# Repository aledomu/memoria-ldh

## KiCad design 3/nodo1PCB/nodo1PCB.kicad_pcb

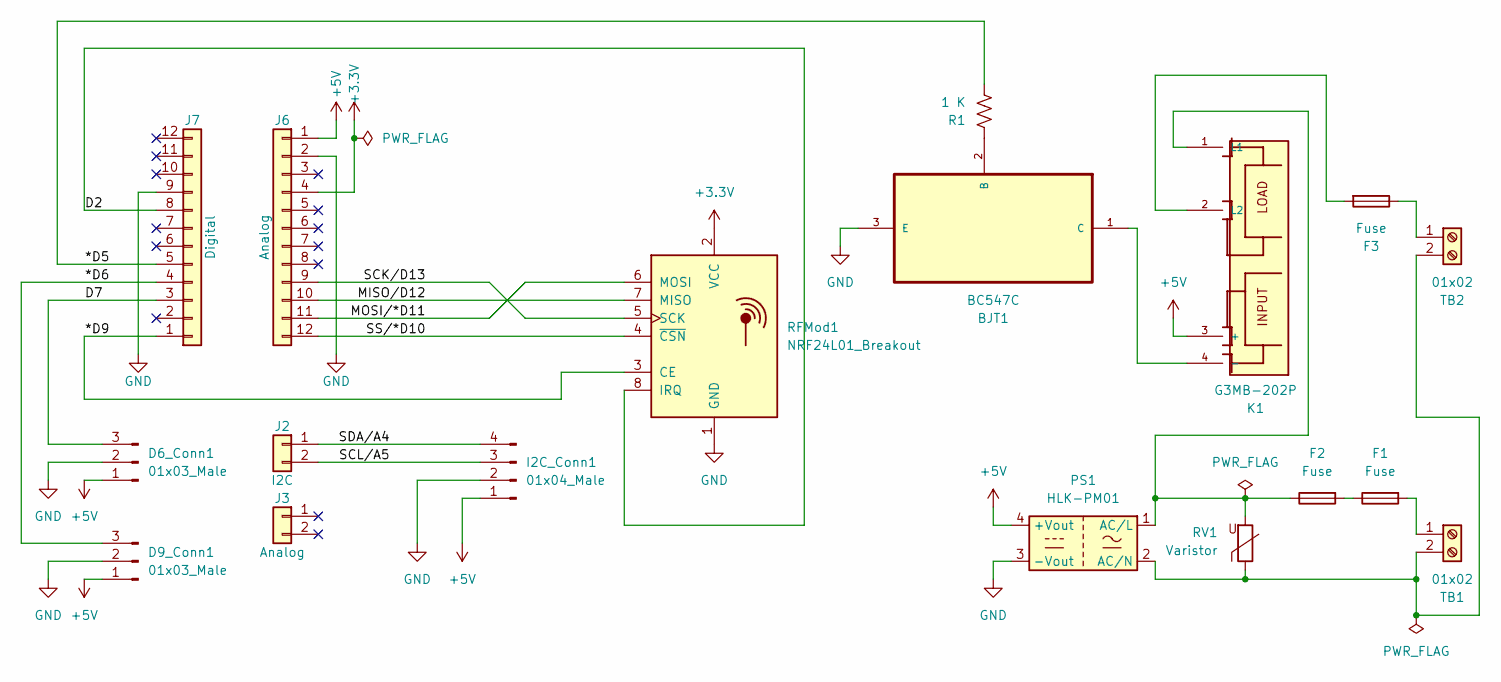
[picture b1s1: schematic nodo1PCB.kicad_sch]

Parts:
BJT1: BC547C; TO127P254X732-3; MPN BC547C
D6_Conn1, D9_Conn1: 01x03_Male; PinHeader_1x03_P2.54mm_Vertical
F1, F2, F3: Fuse; R_Axial_DIN0414_L11.9mm_D4.5mm_P15.24mm_Horizontal
I2C_Conn1: 01x04_Male; PinHeader_1x04_P2.54mm_Vertical
J2: I2C; PinHeader_1x02_P2.54mm_Vertical
J3: Analog; PinHeader_1x02_P2.54mm_Vertical
J6: Analog; PinHeader_1x12_P2.54mm_Vertical
J7: Digital; PinHeader_1x12_P2.54mm_Vertical
K1: G3MB-202P; RELAY_G3MB-202P
PS1: HLK-PM01; Converter_ACDC_HiLink_HLK-PMxx
R1: 1 K; R_1206_3216Metric_Pad1.30x1.75mm_HandSolder
RFMod1: NRF24L01_Breakout; nRF24L01_Breakout
RV1: Varistor; RV_Disc_D12mm_W6.2mm_P7.5mm
TB1, TB2: 01x02; TerminalBlock_bornier-2_P5.08mm

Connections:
+3.3V: J6.4, RFMod1.2 (VCC)
+5V: D6_Conn1.1, D9_Conn1.1, I2C_Conn1.1, J6.1, K1.3 (+), PS1.4 (+Vout)
/*D5: J7.5, R1.2
/*D6: D9_Conn1.3, J7.4
/*D9: J7.1, RFMod1.3 (CE)
/D2: J7.8, RFMod1.8 (IRQ)
/D7: D6_Conn1.3, J7.3
/MISO/D12: J6.10, RFMod1.7 (MISO)
/MOSI/*D11: J6.11, RFMod1.6 (MOSI)
/SCK/D13: J6.9, RFMod1.5 (SCK)
/SCL/A5: I2C_Conn1.3, J2.2
/SDA/A4: I2C_Conn1.4, J2.1
/SS/*D10: J6.12, RFMod1.4 (~CSN)
GND: BJT1.3 (E), D6_Conn1.2, D9_Conn1.2, I2C_Conn1.2, J6.2, J7.9, PS1.3 (-Vout), RFMod1.1 (GND)
unnamed: BJT1.1 (C), K1.4 (-)
unnamed: BJT1.2 (B), R1.1
unnamed: F1.1, F2.2
unnamed: F1.2, TB1.1
unnamed: F2.1, K1.1 (L1), PS1.1 (AC/L), RV1.2
unnamed: F3.1, TB2.1
unnamed: F3.2, K1.2 (L2)
unnamed: PS1.2 (AC/N), RV1.1, TB1.2, TB2.2

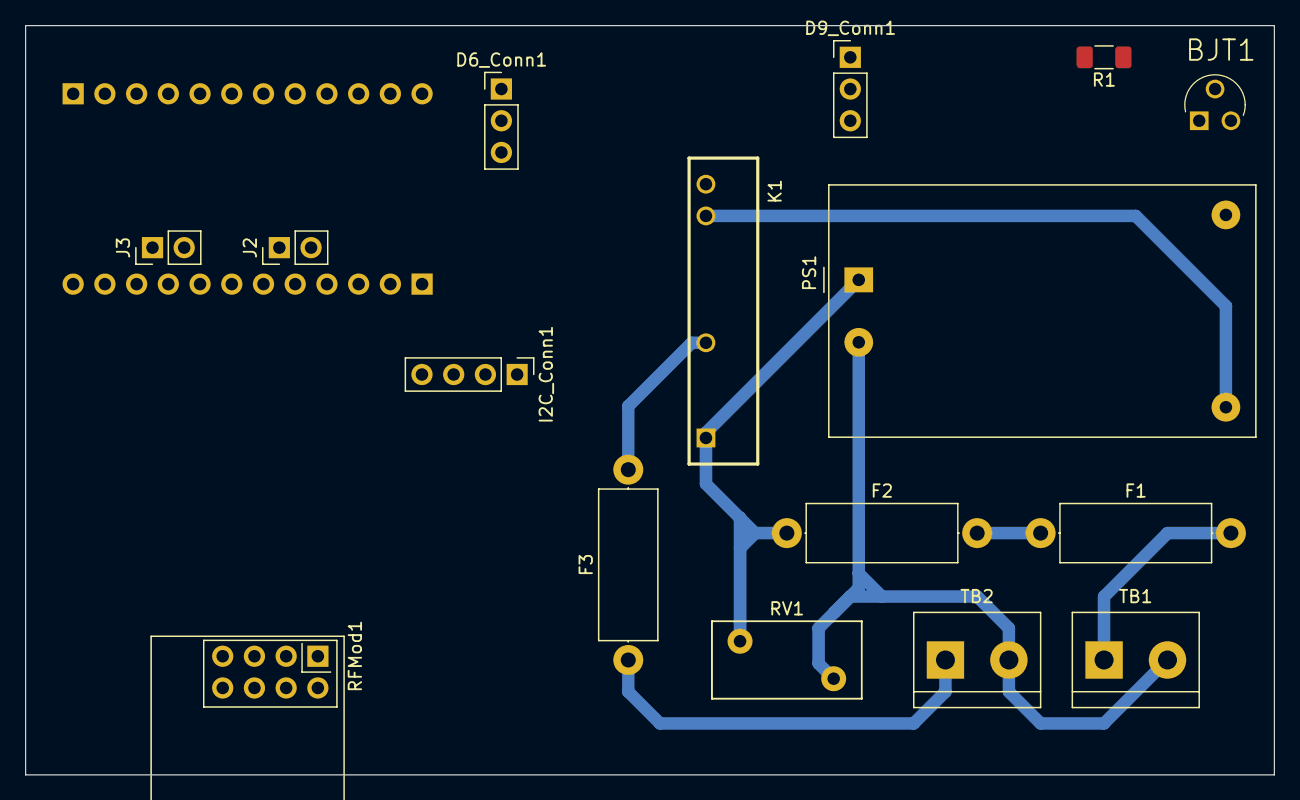
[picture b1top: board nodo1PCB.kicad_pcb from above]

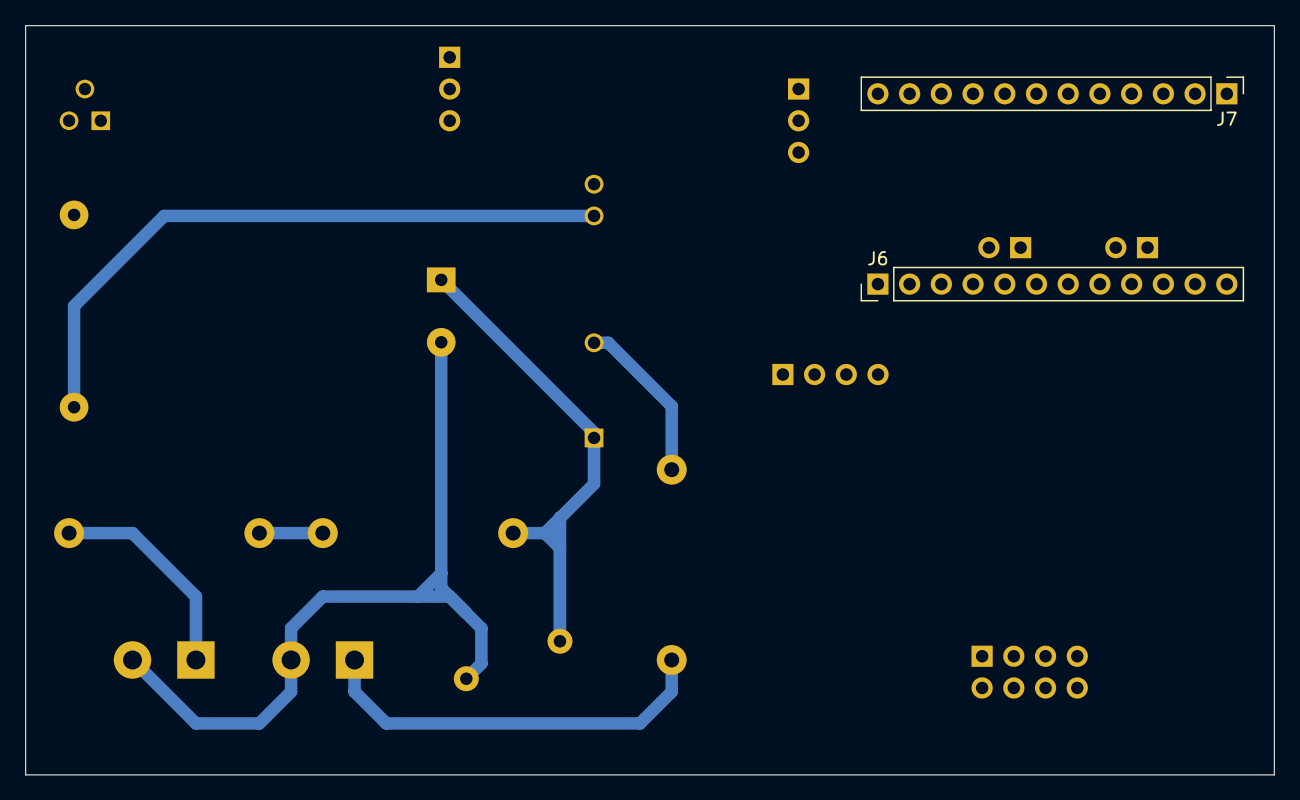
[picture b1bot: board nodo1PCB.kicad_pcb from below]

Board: 2 copper layers, 100.0 x 60.0 mm, 18 parts (2 on the bottom side), 22 nets.

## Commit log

2022-12-11 Initial LaTeX template for VS Code
2023-01-01 Acabar código Nodo 2
2023-01-01 Terminar PCB
2023-01-01 Documentar la selección de procesador de Arduino Pro Mini
2023-01-01 Añadir imágenes del resultado del Nodo 2
2023-01-01 Excluir archivos secundarios del proyecto de la PCB
2023-01-01 Corregir desbordamiento de línea
2023-01-01 Añadir archivos de la memoria de prácticas de LDH
2023-01-01 Añadir referencias a librerías que faltaban
2023-01-01 Crear esqueleto del bloque 3
2023-01-01 Esconder bordes de los enlaces
2023-01-01 Unificar criterios de importación
2023-01-01 Borrar archivos sobrantes del intento de despliegue con Docker Compose
2023-01-01 Indicar reporte de incidencia a MySensors sobre la interfaz GPIO
2023-01-01 Acabar layout alimentación PCB
2023-01-01 Añadir capturas de pantalla de la generación de archivos Gerber
2023-01-01 Documentar la práctica del Nodo 2
2023-01-01 Iniciar la documentación de la PCB
2023-01-16 Dejar la velocidad del UART por defecto
2023-01-27 Añadir soporte para la autenticación de mensajes
2023-01-27 Documentar la creación del PCB
2023-01-27 Actualizar fecha
